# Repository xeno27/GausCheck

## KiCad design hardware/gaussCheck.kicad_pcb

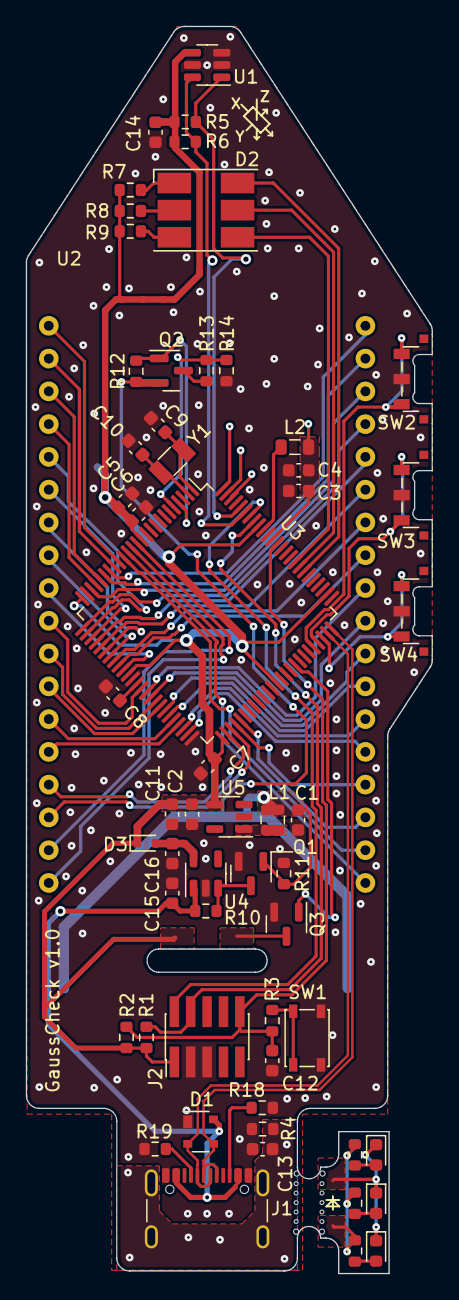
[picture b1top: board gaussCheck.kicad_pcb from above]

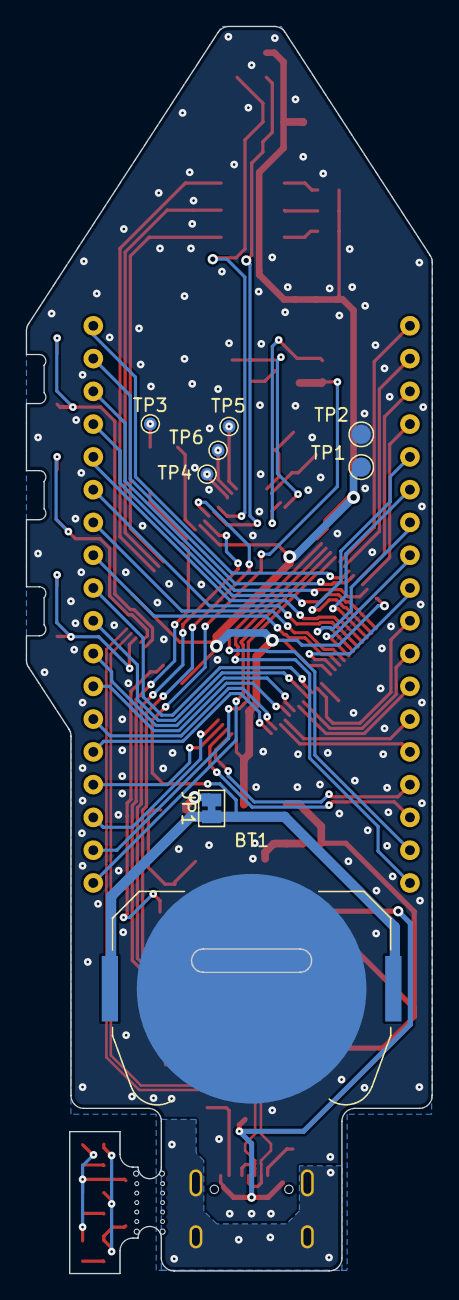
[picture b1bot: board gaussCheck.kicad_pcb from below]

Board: 2 copper layers, 31.5 x 96.7 mm, 66 parts (8 on the bottom side), 81 nets.

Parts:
BT1: Battery_Cell; BatteryHolder_Keystone_3034_1x20mm
C1: 4u7; C_0603_1608Metric
C2, C6, C11: 10u; C_0603_1608Metric
C3, C8, C15, C16: 1u; C_0603_1608Metric
C4, C5, C7, C12, C14: 100n; C_0603_1608Metric
C9, C10: 8p; C_0603_1608Metric
C13: 4n5; C_0603_1608Metric
D1: PRTR5V0U2X; SOT-143
D2: LED_RGB; LED_RGB_Cree-PLCC-6_6x5mm_P2.1mm
D3: RB521S30T1G; D_SOD-523
D4, D5, D6: LED; LED_0603_1608Metric
J1: USB_C_Receptacle_USB2.0; USB_C_Receptacle_GCT_USB4105-xx-A_16P_TopMnt_Horizontal
J2: SWD; PinHeader_2x05_P1.27mm_Vertical_SMD
JP1: IBatt; SolderJumper-2_P1.3mm_Bridged_Pad1.0x1.5mm
L1: 2u2; L_Murata_0806_2.00x1.60mm
L2: 10uH; L_0805_2012Metric
Q1, Q3: BSS138; SOT-23
Q2: BSS83P; SOT-23
R1: 1k; R_0603_1608Metric
R2, R10, R14: 10k; R_0603_1608Metric
R3: 300r; R_0603_1608Metric
R4: 1M; R_0603_1608Metric
R5, R6: 2k2; R_0603_1608Metric
R7: locked; R_0603_1608Metric
R8, R9: 100r; R_0603_1608Metric
R11, R12: 100k; R_0603_1608Metric
R13: 4k7; R_0603_1608Metric
R15, R16, R17: 140; R_0603_1608Metric
R18, R19: 56k; R_0603_1608Metric
SW1: PTS810; SW_SPST_PTS810
SW2, SW3, SW4: PT847S; SW_SPST_CK_PTS847MMxxxSMT_4.6x2.2mm
TP1: 3V3; TestPoint_Pad_D1.5mm
TP2: Gnd; TestPoint_Pad_D1.5mm
TP3, TP4, TP5, TP6: TestPoint; TestPoint_Pad_D1.0mm
U1: TLV493D; SOT-23-6
U2: VIM-878-DP; VIM-878-DP_8x14-segments_52x22mm
U3: ATSAML22N18A-AUT; TQFP-100_14x14mm_P0.5mm
U4: AP2112K-3.3; SOT-23-5
U5: TPS613221ADBV; SOT-23-5
Y1: 32.768kHz; Crystal_SMD_3215-2Pin_3.2x1.5mm

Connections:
+3V3: C2.1, C5.1, C6.1, C7.1, C11.1, C14.1, D3.1 (K), J2.1, R1.1, R2.1, R5.1, R6.1, R7.1, R8.1, R9.1, TP1.1, U1.4 (VDD), U3.12 (VDDANA), U3.25 (VDDANA), U3.36 (VDDIO), U3.51 (VDDIO), U3.63 (VDDIO), U3.77 (VDDIO), U3.92 (VDDIO), U5.4 (VO)
+BATT: BT1.1 (+), JP1.1 (A), Q2.2 (S), R12.1
/DisplayLightning/EN_DisplayLED: Q3.1 (G), U3.67 (PB19/SLCD[45])
/DisplayLightning/LED_A: R15.1, R16.1, R17.1
/DisplayLightning/LED_K: D4.1 (K), D5.1 (K), D6.1 (K)
/MCU/BTN1: SW2.1, U3.71 (PA21/SLCD[49])
/MCU/BTN2: SW3.1, U3.72 (PA22/SERCOM0.2|2.0|I2C/SLCD[50])
/MCU/BTN3: SW4.1, U3.73 (PA23/SERCOM0.3|2.1|I2C/SLCD[51])
/MCU/COM0: U2.17 (COM0), U3.13 (PB06/AIN[14]/SLCD[0])
/MCU/COM1: U2.18 (COM1), U3.14 (PB07/AIN[15]/SLCD[1])
/MCU/COM2: U2.19 (COM2), U3.15 (PB08/AIN[02]/SLCD[2])
/MCU/COM3: U2.20 (COM3), U3.16 (PB09/AIN[03]/SLCD[3])
/MCU/D+: D1.3 (I/O2), J1.A6 (D+), J1.B6 (D+), U3.75 (PA25/D+)
/MCU/D-: D1.2 (I/O1), J1.A7 (D-), J1.B7 (D-), U3.74 (PA24/D-)
/MCU/DEFCA1: U2.1 (1DEFCA), U3.17 (PA04/SLCD[4])
/MCU/DEFCA2: U2.3 (2DEFCA), U3.21 (PC05/SLCD[8])
/MCU/DEFCA3: U2.5 (3DEFCA), U3.27 (PA09/SLCD[12])
/MCU/DEFCA4: U2.7 (4DEFCA), U3.31 (PC09/SLCD[16])
/MCU/DEFCA5: U2.9 (5DEFCA), U3.35 (PC13/SLCD[20])
/MCU/DEFCA6: U2.11 (6DEFCA), U3.42 (PB14/SLCD[24])
/MCU/DEFCA7: U2.13 (7DEFCA), U3.46 (PA12/SERCOM3.0|4.0|I2C/SLCD[28])
/MCU/DEFCA8: U2.15 (8DEFCA), U3.52 (PA16/SLCD[32])
/MCU/DPCBA1: U2.35 (1DPCBA), U3.20 (PA07/SLCD[7])
/MCU/DPCBA2: U2.33 (8DPCBA), U3.26 (PA08/SLCD[11])
/MCU/DPCBA3: U2.31 (8DPCBA), U3.30 (PC08/SLCD[15])
/MCU/DPCBA4: U2.29 (8DPCBA), U3.34 (PC12/SLCD[19])
/MCU/DPCBA5: U2.27 (8DPCBA), U3.41 (PB13/SERCOM3.1|SCL/SLCD[23])
/MCU/DPCBA6: U2.25 (6DPCBA), U3.45 (PC15/SLCD[27])
/MCU/DPCBA7: U2.23 (7DPCBA), U3.49 (PA15/SLCD[31])
/MCU/DPCBA8: U2.21 (8DPCBA), U3.55 (PA19/SLCD[35])
/MCU/EN_VBat: Q2.1 (G), R12.2, U3.4 (PC01/AIN[17])
/MCU/LED1: D2.6 (RA), U3.82 (PC24)
/MCU/LED2: D2.5 (GA), U3.83 (PC25)
/MCU/LED3: D2.4 (BA), U3.84 (PC26)
/MCU/LKJI1: U2.2 (1LKJI), U3.18 (PA05/SLCD[5])
/MCU/LKJI2: U2.4 (2LKJI), U3.22 (PC06/SLCD[9})
/MCU/LKJI3: U2.6 (3LKJI), U3.28 (PA10/SLCD[13])
/MCU/LKJI4: U2.8 (4LKJI), U3.32 (PC10/SLCD[17])
/MCU/LKJI5: U2.10 (5LKJI), U3.39 (PB11/SLCD[21])
/MCU/LKJI6: U2.12 (6LKJI), U3.43 (PB15/SLCD[25])
/MCU/LKJI7: U2.14 (7LKJI), U3.47 (PA13/SERCOM3.1|4.1|I2C/SLCD[29])
/MCU/LKJI8: U2.16 (8LKJI), U3.53 (PA17/SLCD[33])
/MCU/MNGH1: U2.36 (1MNGH), U3.19 (PA06/SLCD[6])
/MCU/MNGH2: U2.34 (8MNGH), U3.23 (PC07/SLCD[10])
/MCU/MNGH3: U2.32 (8MNGH), U3.29 (PA11/SLCD[14])
/MCU/MNGH4: U2.30 (8MNGH), U3.33 (PC11/SLCD[18])
/MCU/MNGH5: U2.28 (8MNGH), U3.40 (PB12/SERCOM3.0|SDA/SLCD[22])
/MCU/MNGH6: U2.26 (6MNGH), U3.44 (PC14/SLCD[26])
/MCU/MNGH7: U2.24 (7MNGH), U3.48 (PA14/SLCD[30])
/MCU/MNGH8: U2.22 (8MNGH), U3.54 (PA18/SLCD[34])
/MCU/SCL: R5.2, U1.1 (SCL/INT), U3.96 (PB31/SERCOM1.1|5.1|SCL)
/MCU/SDA: R6.2, U1.6 (SDA/ADDR), U3.95 (PB30/SERCOM1.0|5.0|SDA)
/MCU/SWCLK: J2.4, R1.2, U3.93 (PA30/SWCLK)
/MCU/SWDIO: J2.2, U3.94 (PA31/SWDIO)
/MCU/Sense_VBat: R13.2, R14.2, U3.5 (PC02/AIN[18])
/MCU/VDDCORE: C3.1, C4.1, L2.2, TP3.1, U3.89 (VDDCORE)
/MCU/~RESET: C12.1, J2.10, R2.2, R3.1, U3.88 (RESET)
/Power/BATT: C1.1, JP1.2 (B), L1.1, Q1.1 (G), R11.2
/Power/BATT_SW: L1.2, U5.1 (SW)
GND: BT1.2 (-), C1.2, C2.2, C3.2, C4.2, C5.2, C6.2, C7.2, C8.2, C9.1, C10.1, C11.2, C12.2, C13.2, C14.2, C15.2, C16.2, D1.1 (GND), J1.A1 (GND), J1.A12 (GND), J1.B1 (GND), J1.B12 (GND), J2.3, J2.5, Q1.2 (S), Q3.2 (S), R4.2, R11.1, R14.1, R18.2, R19.2, SW1.2, SW2.2, SW3.2, SW4.2, TP2.1, U1.2 (GND), U1.3 (GND), U1.5 (GND), U3.11 (GND), U3.24 (GND), U3.37 (GND), U3.50 (GND), U3.62 (GND), U3.76 (GND), U3.90 (GND), U4.2 (GND), U5.2 (GND)
unnamed: D2.3 (BK), R9.2
unnamed: D2.2 (GK), R8.2
unnamed: D2.1 (RK), R7.2
unnamed: C16.1, D3.2 (A), U4.5 (VOUT)
unnamed: D4.2 (A), R15.2
unnamed: D5.2 (A), R16.2
unnamed: D6.2 (A), R17.2
unnamed: J1.A5 (CC1), R19.1
unnamed: J1.B5 (CC2), R18.1
unnamed: C13.1, J1.S1 (SHIELD), R4.1
unnamed: Q1.3 (D), R10.2, U4.3 (EN)
unnamed: Q2.3 (D), R13.1
unnamed: R3.2, SW1.1
unnamed: C9.2, U3.1 (PA00/XIN32/I0/SERCOM1.0), Y1.1
unnamed: C10.2, U3.2 (PA01/XOUT32/I1/SERCOM1.1), Y1.2
unnamed: TP4.1, U3.98 (PB01/AIN[09])
unnamed: TP6.1, U3.99 (PB02/AIN[10])
unnamed: TP5.1, U3.100 (PB03/AIN[11])
unnamed: L2.1, U3.91 (VDDOUT)
unnamed: C8.1, U3.38 (VLCD)
VBUS: C15.1, D1.4 (VCC), J1.A4 (VBUS), J1.A9 (VBUS), J1.B4 (VBUS), J1.B9 (VBUS), R10.1, U4.1 (VIN)

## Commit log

2023-12-07 create hardware folder and license
2023-12-07 fix typo, add sw folder
2023-12-08 new KiCAD Project made SAML22 symbol made VIM-878 symbol and footprint
2023-12-13 add block diagram
2023-12-21 add datasheet
2023-12-21 SCH - display lines
2023-12-21 more schematic work, added buttons and led lcd wiring done
2023-12-25 try to organise on pcb
2023-12-25 continue
2023-12-26 change btn in sch, routing
2024-01-04 added 3Dmodel for Display centered and locked key components
2024-01-04 added 3D models to pushbuttons
2024-01-04 changed USB-C connector to GCT_USB4105 in favor for a 3D model
2024-01-04 Turned MCU by 45degress and rerouted
2024-01-05 3v3 routing, change L2 to 0805 component
2024-01-05 via stitching, board outline, silkscreen
2024-01-05 added a nice render
2024-01-05 minor adjustments
2024-01-05 moved buttons to the side JTAG to the bottom reset to the bottom
2024-01-05 added 3V3 LDO added VBat Measurement
2024-02-05 added schottky diode to LDO connected en_vbat signal added a drawing of mems axis
2024-02-05 fixed Batposition DRC checked!
2024-02-05 updated some MPNs
2024-02-05 change LCD MPN
2024-02-05 added daughter board for LCD lightning
2024-02-05 custom LED daughter board for display lightning added resistors to USB-C CC line
2024-02-06 fixed battery footprint
2024-02-06 updated daughter board for 1.8mm mill
2024-02-17 update Mouser Nr..
2024-02-17 change debug connector..
